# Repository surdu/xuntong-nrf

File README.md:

See [specs on wiki](https://github.com/surdu/xuntong-nrf/wiki/Specs) for board pinout and dimmenstions.

## The breakout

## The board

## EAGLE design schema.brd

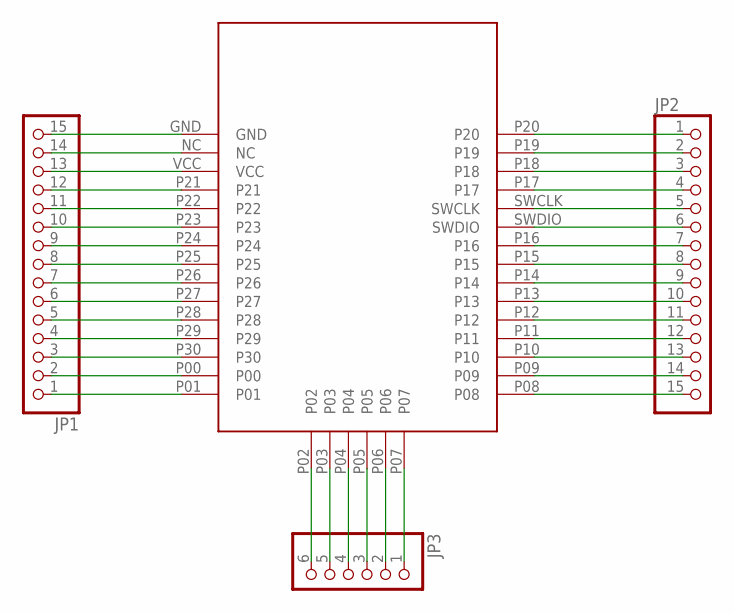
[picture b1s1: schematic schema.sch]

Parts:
JP1, JP2: PINHD-1X15; 1X15
JP3: PINHD-1X6; 1X06
U$1: XUNTONG; SMD

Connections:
unnamed: JP1.15, U$1.GND
unnamed: JP1.14, U$1.NC
unnamed: JP1.13, U$1.VCC
unnamed: JP1.12, U$1.P21
unnamed: JP1.11, U$1.P22
unnamed: JP1.10, U$1.P23
unnamed: JP1.9, U$1.P24
unnamed: JP1.8, U$1.P25
unnamed: JP1.7, U$1.P26
unnamed: JP1.6, U$1.P27
unnamed: JP1.5, U$1.P28
unnamed: JP1.4, U$1.P29
unnamed: JP1.3, U$1.P30
unnamed: JP1.2, U$1.P00
unnamed: JP1.1, U$1.P01
unnamed: JP3.6, U$1.P02
unnamed: JP3.5, U$1.P03
unnamed: JP3.4, U$1.P04
unnamed: JP3.3, U$1.P05
unnamed: JP3.2, U$1.P06
unnamed: JP3.1, U$1.P07
unnamed: JP2.1, U$1.P20
unnamed: JP2.2, U$1.P19
unnamed: JP2.3, U$1.P18
unnamed: JP2.4, U$1.P17
unnamed: JP2.5, U$1.SWCLK
unnamed: JP2.6, U$1.SWDIO
unnamed: JP2.7, U$1.P16
unnamed: JP2.8, U$1.P15
unnamed: JP2.9, U$1.P14
unnamed: JP2.10, U$1.P13
unnamed: JP2.11, U$1.P12
unnamed: JP2.12, U$1.P11
unnamed: JP2.13, U$1.P10
unnamed: JP2.14, U$1.P09
unnamed: JP2.15, U$1.P08

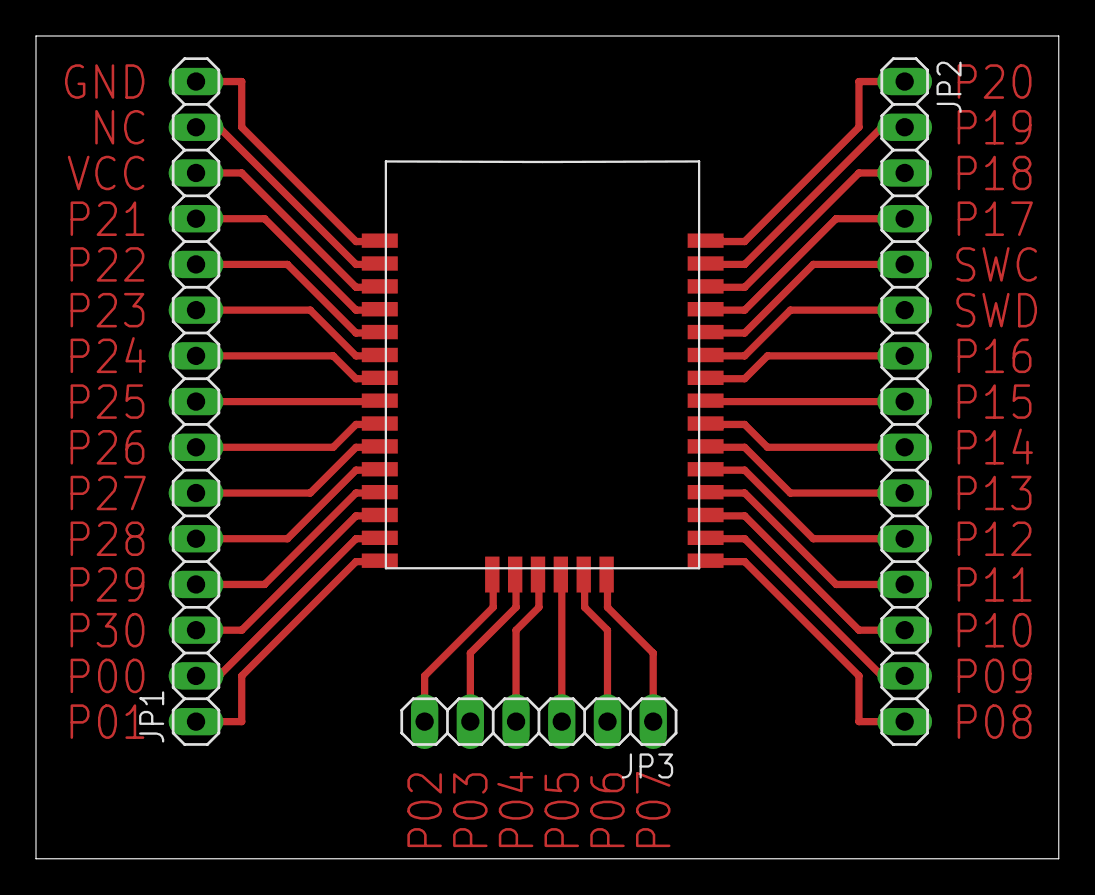
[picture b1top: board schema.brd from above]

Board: 2 copper layers, 56.8 x 45.7 mm, 4 parts (0 on the bottom side), 36 nets.

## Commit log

2015-11-19 Added the board and schematic
